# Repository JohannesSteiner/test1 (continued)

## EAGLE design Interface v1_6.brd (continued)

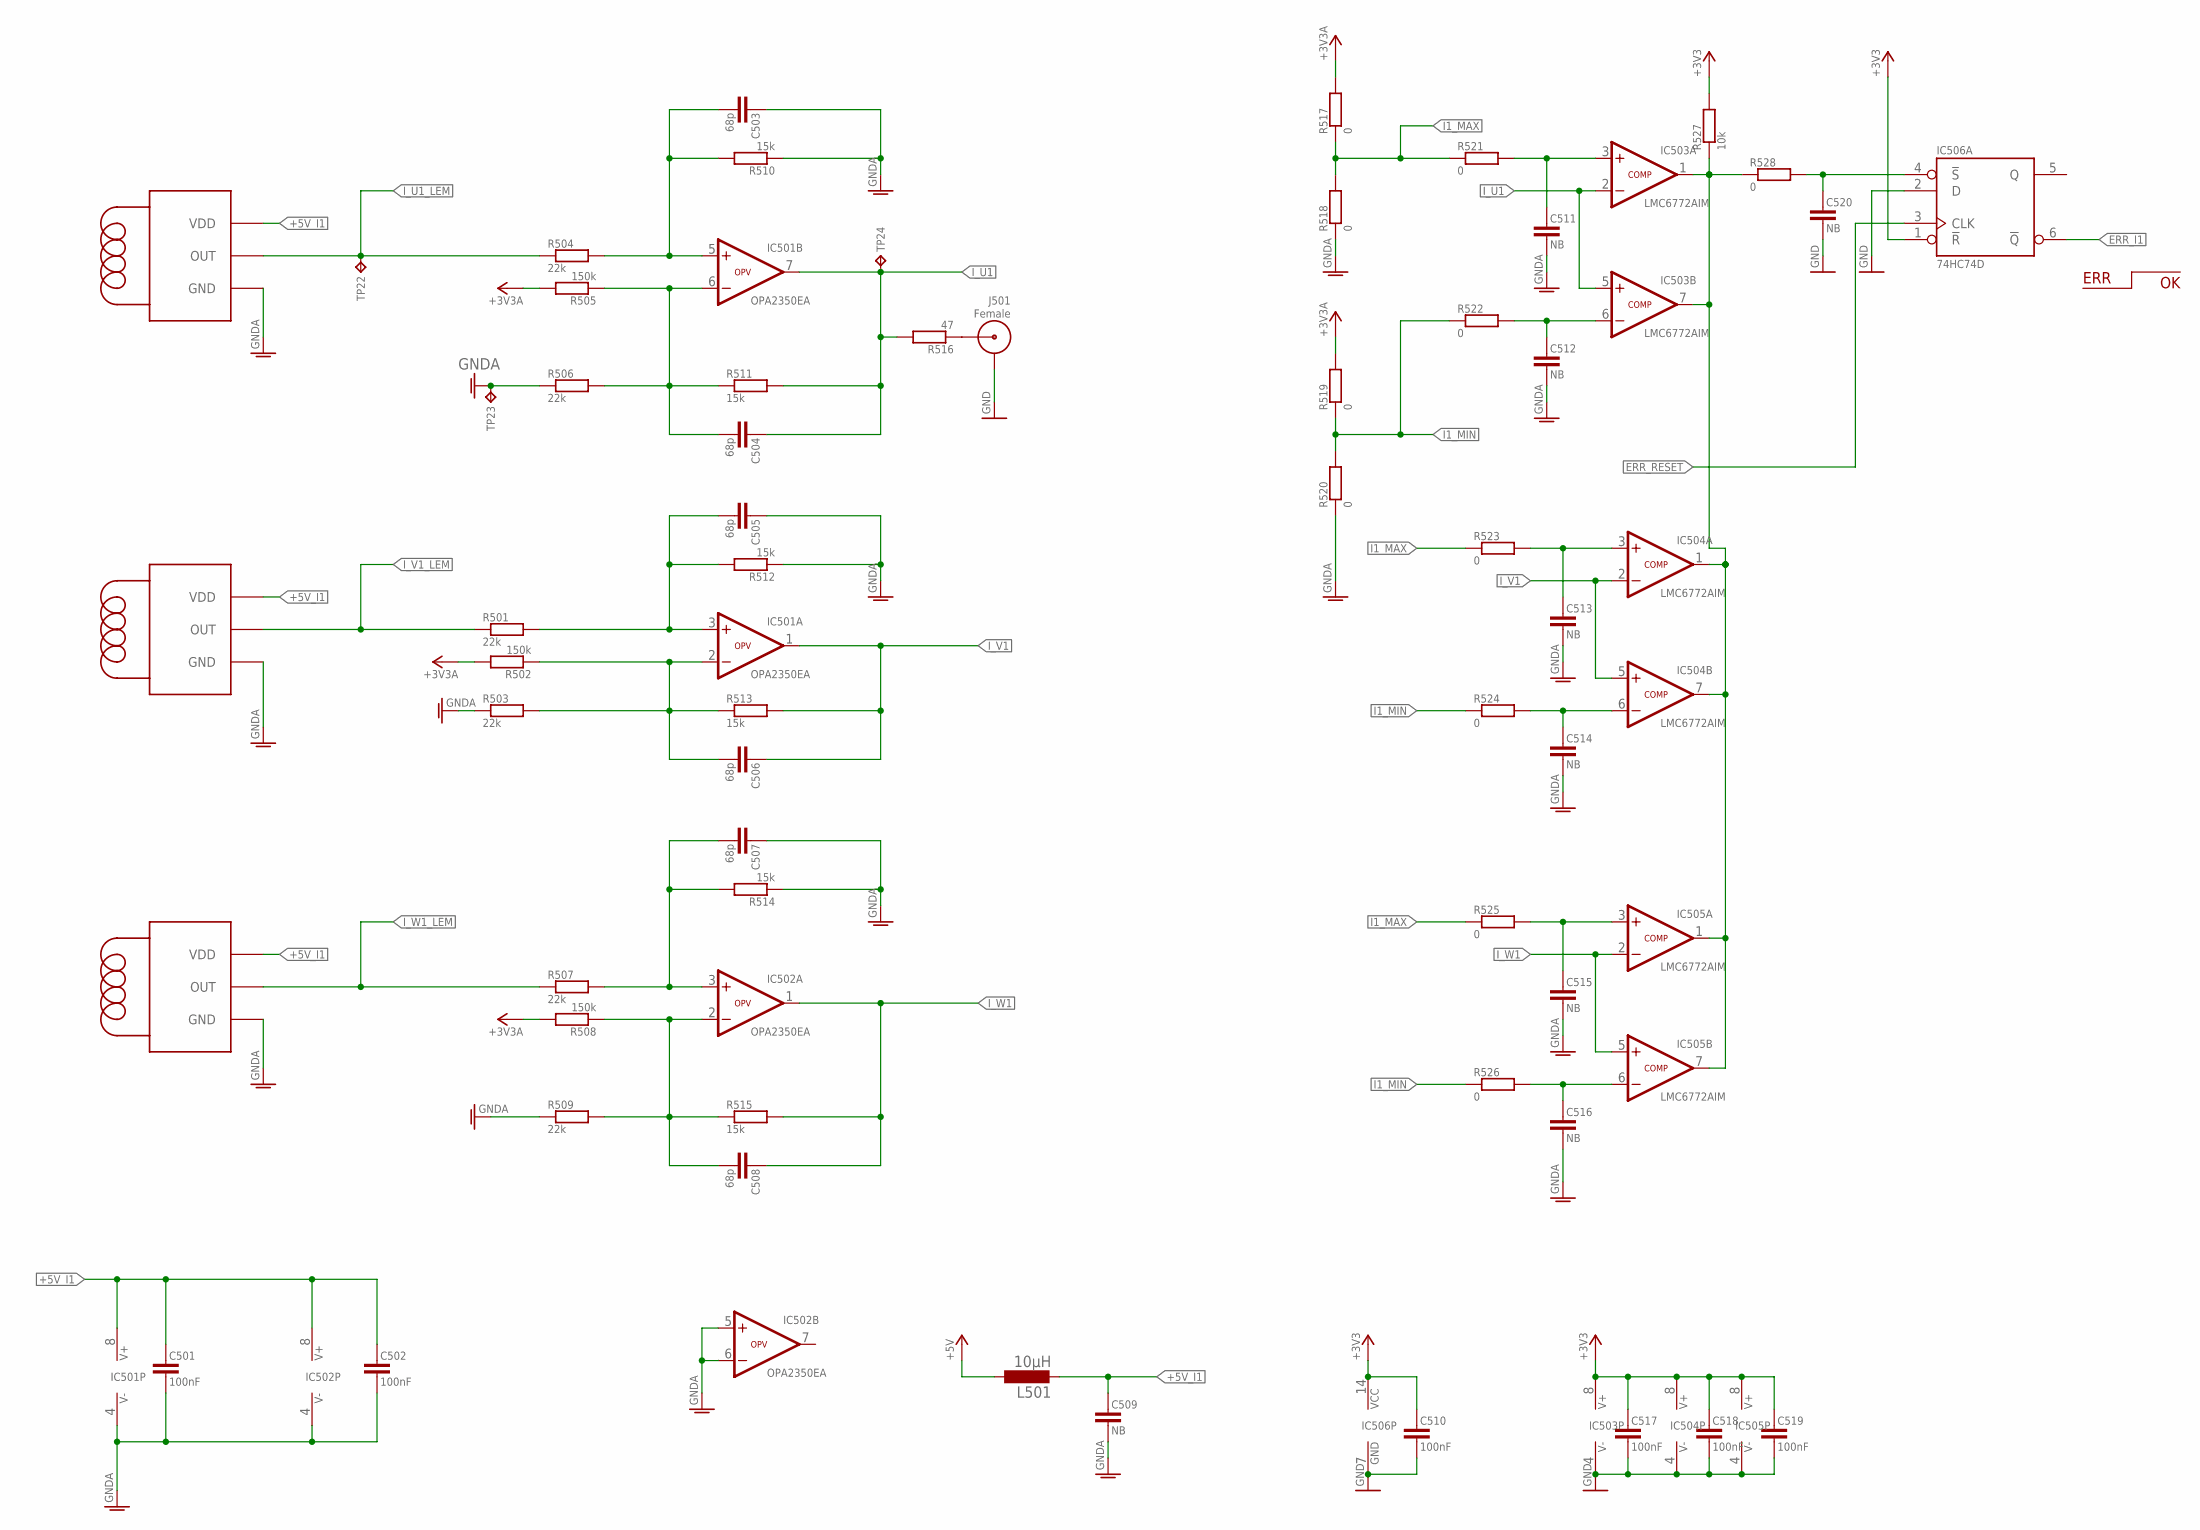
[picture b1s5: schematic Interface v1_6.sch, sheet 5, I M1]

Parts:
C501, C502, C510, C517, C518, C519: 100nF; C-0805"
C503, C504, C505, C506, C507, C508: 68p; C-0805"
C509, C511, C512, C513, C514, C515, C516, C520: NB; C-0805"
I501, I502, I503: HC2F
IC501, IC502: OPA2350EA; SOIC8
IC503, IC504, IC505: LMC6772AIM; SOIC8
IC506: 74HC74D; SOIC14
J501: Female; SMA_KLEIN
L501: 10µH; L3230M
R501, R503, R504, R506, R507, R509: 22k; R-0805"
R502, R505, R508: 150k; R-0805"
R510, R511, R512, R513, R514, R515: 15k; R-0805"
R516: 47; R-0805"
R517, R518, R519, R520, R521, R522, R523, R524, R525, R526, R528: 0; R-0805"
R527: 10k; R-0805"
TP22, TP24: TP-TH-08; TP-08
TP23: TP-TH-12; TP-12

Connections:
+3V3: C510.1, C517.1, C518.1, C519.1, IC503.8 (V+), IC504.8 (V+), IC505.8 (V+), IC506.1 (!R), IC506.14 (VCC), R527.2; also elsewhere on the board
+3V3A_I1: R502.2, R505.2, R508.2, R517.2, R519.2; also elsewhere on the board
+5V: L501.1; also elsewhere on the board
+5V_I1: C501.1, C502.1, C509.1, I501.3 (VDD), I502.3 (VDD), I503.3 (VDD), IC501.8 (V+), IC502.8 (V+), L501.2; also elsewhere on the board
ERR_I1: IC506.6 (!Q); also elsewhere on the board
ERR_RESET: IC506.3 (CLK); also elsewhere on the board
GND: C510.2, C517.2, C518.2, C519.2, C520.2, IC503.4 (V-), IC504.4 (V-), IC505.4 (V-), IC506.2 (D), IC506.7 (GND), J501.1 (GND), J501.3 (GND), J501.4 (GND), J501.5 (GND); also elsewhere on the board
GNDA: C501.2, C502.2, C503.1, C505.1, C507.1, C509.2, C511.2, C512.2, C513.2, C514.2, C515.2, C516.2, I501.2 (GND), I501.E1 (GND), I501.E2 (GND), I501.E3 (GND), I501.E4 (GND), I502.2 (GND), I502.E1 (GND), I502.E2 (GND), I502.E3 (GND), I502.E4 (GND), I503.2 (GND), I503.E1 (GND), I503.E2 (GND), I503.E3 (GND), I503.E4 (GND), IC501.4 (V-), IC502.4 (V-), IC502.5 (+IN), IC502.6 (-IN), R503.1, R506.1, R509.1, R510.1, R512.1, R514.1, R518.1, R520.1, TP23.TP; also elsewhere on the board
I1_MAX: R517.1, R518.2, R521.1, R523.1, R525.1
I1_MIN: R519.1, R520.2, R522.1, R524.1, R526.1
I_U1: C504.1, IC501.7 (OUT), IC503.2 (-IN), IC503.5 (+IN), R511.2, R516.2, TP24.TP; also elsewhere on the board
I_U1_LEM: I501.1 (OUT), R504.1, TP22.TP
I_V1: C506.1, IC501.1 (OUT), IC504.2 (-IN), IC504.5 (+IN), R513.2; also elsewhere on the board
I_V1_LEM: I502.1 (OUT), R501.1
I_W1: C508.1, IC502.1 (OUT), IC505.2 (-IN), IC505.5 (+IN), R515.2; also elsewhere on the board
I_W1_LEM: I503.1 (OUT), R507.1
MINUS: C508.2, IC502.2 (-IN), R508.1, R509.2, R515.1
unnamed: C503.2, IC501.5 (+IN), R504.2, R510.2
unnamed: C504.2, IC501.6 (-IN), R505.1, R506.2, R511.1
unnamed: C506.2, IC501.2 (-IN), R502.1, R503.2, R513.1
unnamed: J501.SIG, R516.1
unnamed: C505.2, IC501.3 (+IN), R501.2, R512.2
unnamed: C512.1, IC503.6 (-IN), R522.2
unnamed: C511.1, IC503.3 (+IN), R521.2
unnamed: C520.1, IC506.4 (!S), R528.2
unnamed: C514.1, IC504.6 (-IN), R524.2
unnamed: C513.1, IC504.3 (+IN), R523.2
unnamed: C515.1, IC505.3 (+IN), R525.2
unnamed: C516.1, IC505.6 (-IN), R526.2
OC_M1: IC503.1 (OUT), IC503.7 (OUT), IC504.1 (OUT), IC504.7 (OUT), IC505.1 (OUT), IC505.7 (OUT), R527.1, R528.1
PLUS: C507.2, IC502.3 (+IN), R507.2, R514.2

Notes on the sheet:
ERR

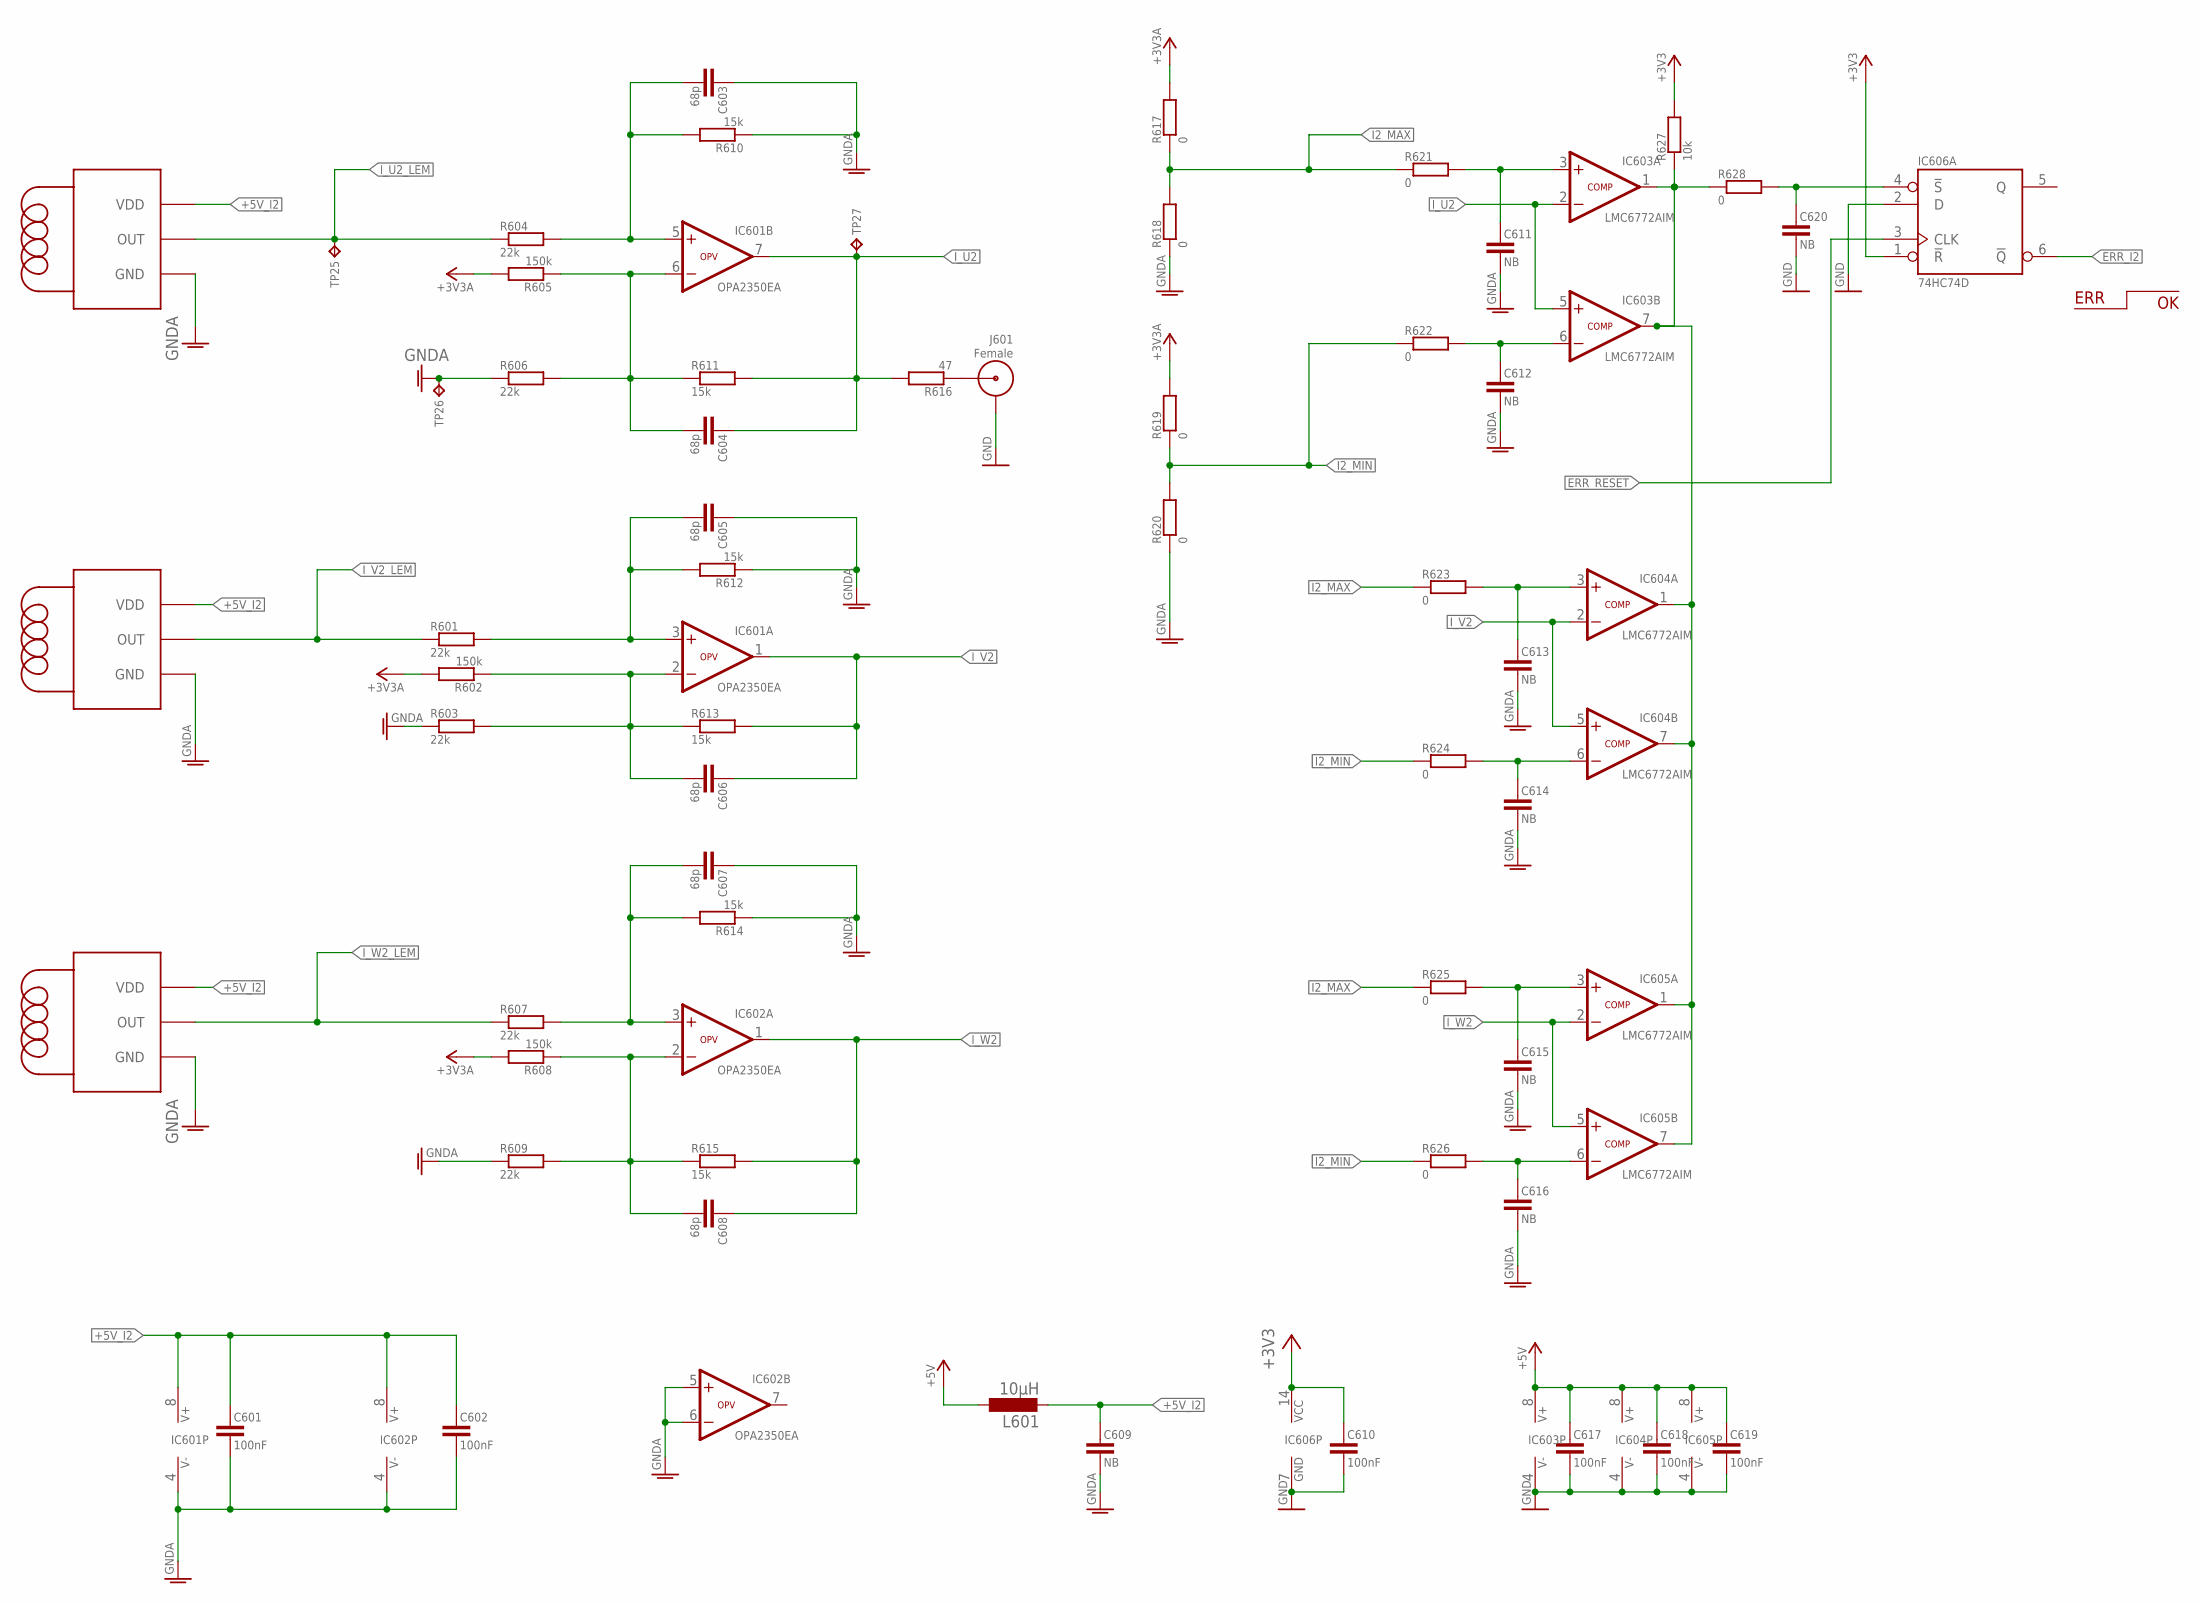
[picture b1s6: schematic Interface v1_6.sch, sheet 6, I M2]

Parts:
C601, C602, C610, C617, C618, C619: 100nF; C-0805"
C603, C604, C605, C606, C607, C608: 68p; C-0805"
C609, C611, C612, C613, C614, C615, C616, C620: NB; C-0805"
I601, I602, I603: HC2F
IC601, IC602: OPA2350EA; SOIC8
IC603, IC604, IC605: LMC6772AIM; SOIC8
IC606: 74HC74D; SOIC14
J601: Female; SMA_KLEIN
L601: 10µH; L3230M
R601, R603, R604, R606, R607, R609: 22k; R-0805"
R602, R605, R608: 150k; R-0805"
R610, R611, R612, R613, R614, R615: 15k; R-0805"
R616: 47; R-0805"
R617, R618, R619, R620, R621, R622, R623, R624, R625, R626, R628: 0; R-0805"
R627: 10k; R-0805"
TP25, TP27: TP-TH-08; TP-08
TP26: TP-TH-12; TP-12

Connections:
+3V3: C610.1, IC606.1 (!R), IC606.14 (VCC), R627.2; also elsewhere on the board
+3V3A_I2: R602.2, R605.2, R608.2, R617.2, R619.2; also elsewhere on the board
+5V: C617.1, C618.1, C619.1, IC603.8 (V+), IC604.8 (V+), IC605.8 (V+), L601.1; also elsewhere on the board
+5V_I2: C601.1, C602.1, C609.1, I601.3 (VDD), I602.3 (VDD), I603.3 (VDD), IC601.8 (V+), IC602.8 (V+), L601.2; also elsewhere on the board
ERR_I2: IC606.6 (!Q); also elsewhere on the board
ERR_RESET: IC606.3 (CLK); also elsewhere on the board
GND: C610.2, C617.2, C618.2, C619.2, C620.2, IC603.4 (V-), IC604.4 (V-), IC605.4 (V-), IC606.2 (D), IC606.7 (GND), J601.1 (GND), J601.3 (GND), J601.4 (GND), J601.5 (GND); also elsewhere on the board
GNDA: C601.2, C602.2, C603.1, C605.1, C607.1, C609.2, C611.2, C612.2, C613.2, C614.2, C615.2, C616.2, I601.2 (GND), I601.E1 (GND), I601.E2 (GND), I601.E3 (GND), I601.E4 (GND), I602.2 (GND), I602.E1 (GND), I602.E2 (GND), I602.E3 (GND), I602.E4 (GND), I603.2 (GND), I603.E1 (GND), I603.E2 (GND), I603.E3 (GND), I603.E4 (GND), IC601.4 (V-), IC602.4 (V-), IC602.5 (+IN), IC602.6 (-IN), R603.1, R606.1, R609.1, R610.1, R612.1, R614.1, R618.1, R620.1, TP26.TP; also elsewhere on the board
I2_MAX: R617.1, R618.2, R621.1, R623.1, R625.1
I2_MIN: R619.1, R620.2, R622.1, R624.1, R626.1
I_U2: C604.1, IC601.7 (OUT), IC603.2 (-IN), IC603.5 (+IN), R611.2, R616.2, TP27.TP; also elsewhere on the board
I_U2_LEM: I601.1 (OUT), R604.1, TP25.TP
I_V2: C606.1, IC601.1 (OUT), IC604.2 (-IN), IC604.5 (+IN), R613.2; also elsewhere on the board
I_V2_LEM: I602.1 (OUT), R601.1
I_W2: C608.1, IC602.1 (OUT), IC605.2 (-IN), IC605.5 (+IN), R615.2; also elsewhere on the board
I_W2_LEM: I603.1 (OUT), R607.1
MINUS2: C608.2, IC602.2 (-IN), R608.1, R609.2, R615.1
unnamed: C612.1, IC603.6 (-IN), R622.2
unnamed: C611.1, IC603.3 (+IN), R621.2
unnamed: C620.1, IC606.4 (!S), R628.2
unnamed: C614.1, IC604.6 (-IN), R624.2
unnamed: C613.1, IC604.3 (+IN), R623.2
unnamed: C615.1, IC605.3 (+IN), R625.2
unnamed: C616.1, IC605.6 (-IN), R626.2
unnamed: C604.2, IC601.6 (-IN), R605.1, R606.2, R611.1
unnamed: C603.2, IC601.5 (+IN), R604.2, R610.2
unnamed: C606.2, IC601.2 (-IN), R602.1, R603.2, R613.1
unnamed: C605.2, IC601.3 (+IN), R601.2, R612.2
unnamed: J601.SIG, R616.1
OC_M2: IC603.1 (OUT), IC603.7 (OUT), IC604.1 (OUT), IC604.7 (OUT), IC605.1 (OUT), IC605.7 (OUT), R627.1, R628.1
PLUS2: C607.2, IC602.3 (+IN), R607.2, R614.2

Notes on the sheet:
ERR

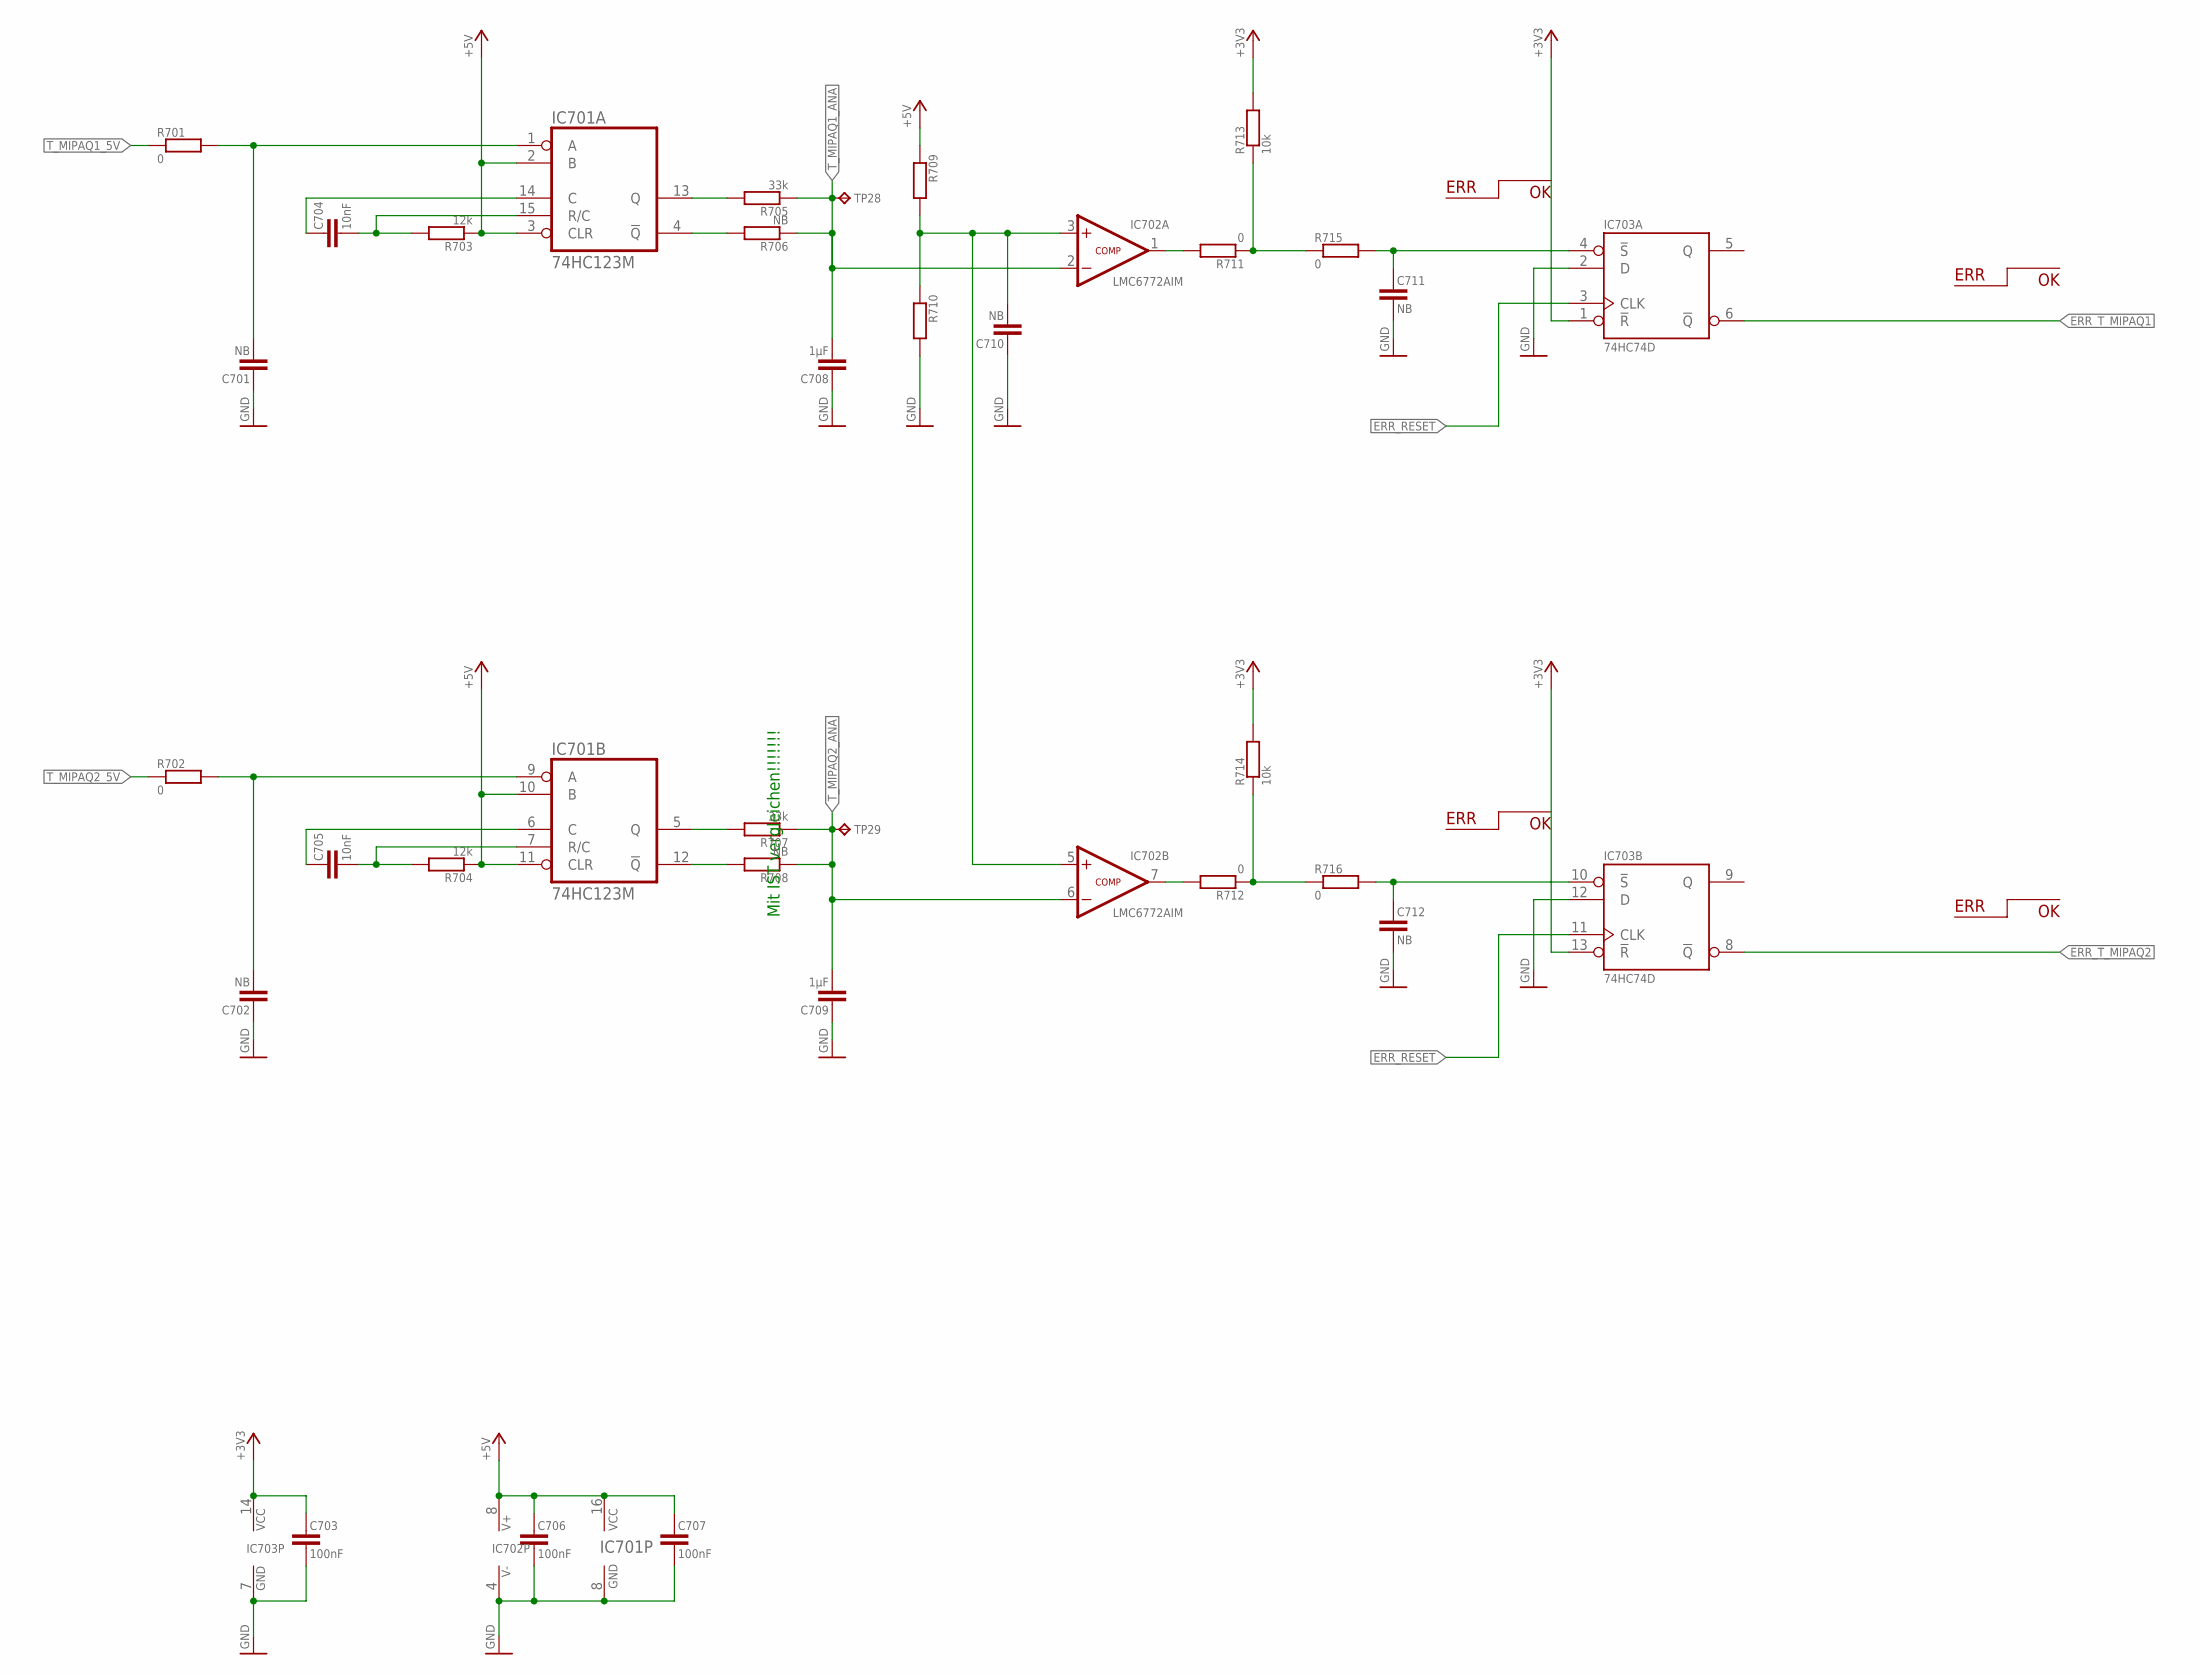
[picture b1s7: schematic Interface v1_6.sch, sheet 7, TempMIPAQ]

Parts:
C701, C702, C710, C711, C712: NB; C-0805"
C703, C706, C707: 100nF; C-0805"
C704, C705: 10nF; C-0805"
C708, C709: 1µF; C-0805"
IC701: 74HC123M; SO16
IC702: LMC6772AIM; SOIC8
IC703: 74HC74D; SOIC14
R701, R702, R711, R712, R715, R716: 0; R-0805"
R703, R704: 12k; R-0805"
R705, R707: 33k; R-0805"
R706, R708: NB; R-0805"
R709, R710: R-0805"
R713, R714: 10k; R-0805"
TP28, TP29: TP-TH-08; TP-08

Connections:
+3V3: C703.1, IC703.1 (!R), IC703.13 (!R), IC703.14 (VCC), R713.2, R714.2; also elsewhere on the board
+5V: C706.1, C707.1, IC701.2 (B), IC701.3 (CLR), IC701.10 (B), IC701.11 (CLR), IC701.16 (VCC), IC702.8 (V+), R703.1, R704.1, R709.1; also elsewhere on the board
ERR_RESET: IC703.3 (CLK), IC703.11 (CLK); also elsewhere on the board
ERR_T_MIPAQ1: IC703.6 (!Q); also elsewhere on the board
ERR_T_MIPAQ2: IC703.8 (!Q); also elsewhere on the board
GND: C701.1, C702.1, C703.2, C706.2, C707.2, C708.1, C709.1, C710.1, C711.2, C712.2, IC701.8 (GND), IC702.4 (V-), IC703.2 (D), IC703.7 (GND), IC703.12 (D), R710.2; also elsewhere on the board
unnamed: IC702.7 (OUT), R712.2
unnamed: IC702.1 (OUT), R711.2
unnamed: C702.2, IC701.9 (A), R702.2
unnamed: IC701.13 (Q), R705.2
unnamed: C701.2, IC701.1 (A), R701.2
unnamed: C704.2, IC701.15 (R/C), R703.2
unnamed: IC701.4 (!Q), R706.2
unnamed: C710.2, IC702.3 (+IN), IC702.5 (+IN), R709.2, R710.1
unnamed: R711.1, R713.1, R715.1
unnamed: C704.1, IC701.14 (C)
unnamed: C705.2, IC701.7 (R/C), R704.2
unnamed: IC701.5 (Q), R707.2
unnamed: IC701.12 (!Q), R708.2
unnamed: C712.1, IC703.10 (!S), R716.2
unnamed: C705.1, IC701.6 (C)
unnamed: R712.1, R714.1, R716.1
unnamed: C711.1, IC703.4 (!S), R715.2
T_MIPAQ1_5V: R701.1; also elsewhere on the board
T_MIPAQ1_ANA: C708.2, IC702.2 (-IN), R705.1, R706.1, TP28.TP; also elsewhere on the board
T_MIPAQ2_5V: R702.1; also elsewhere on the board
T_MIPAQ2_ANA: C709.2, IC702.6 (-IN), R707.1, R708.1, TP29.TP; also elsewhere on the board

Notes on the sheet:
ERR
Mit IST vergleichen!!!!!!!

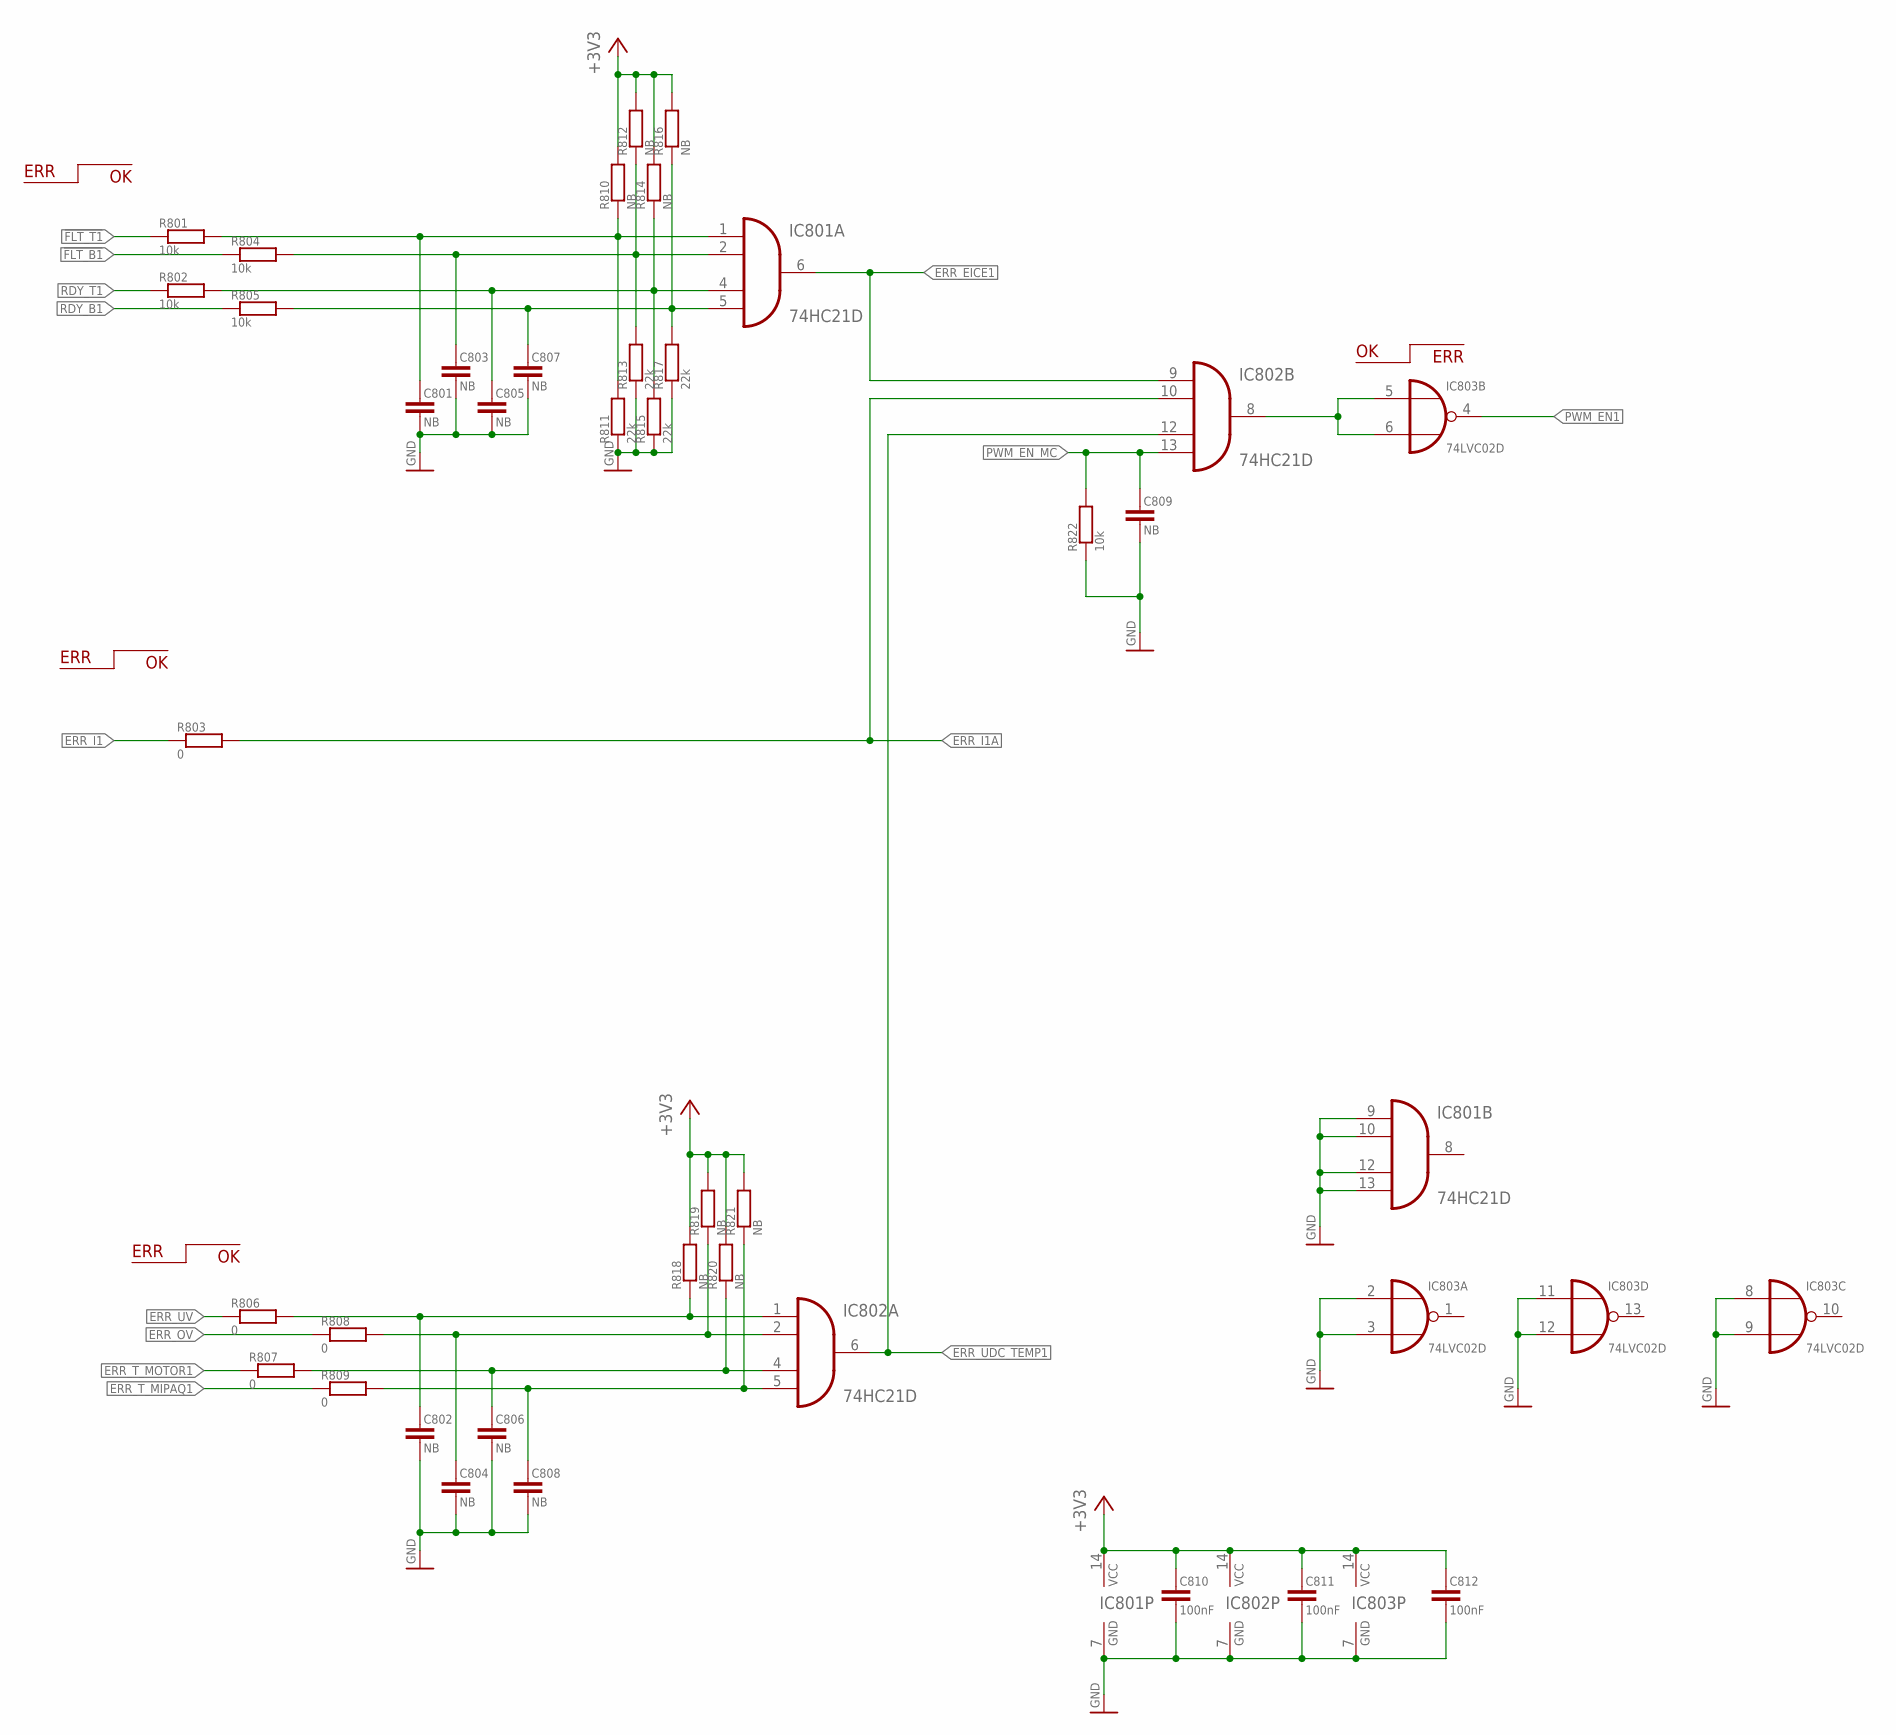
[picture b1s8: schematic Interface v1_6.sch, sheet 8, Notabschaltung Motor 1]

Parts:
C801, C802, C803, C804, C805, C806, C807, C808, C809: NB; C-0805"
C810, C811, C812: 100nF; C-0805"
IC801, IC802: 74HC21D; SOIC14
IC803: 74LVC02D; SOIC14
R801, R802, R804, R805, R822: 10k; R-0805"
R803, R806, R807, R808, R809: 0; R-0805"
R810, R812, R814, R816, R818, R819, R820, R821: NB; R-0805"
R811, R813, R815, R817: 22k; R-0805"

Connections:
!FLT_B1: R804.1; also elsewhere on the board
!FLT_T1: R801.1; also elsewhere on the board
+3V3: C810.1, C811.1, C812.1, IC801.14 (VCC), IC802.14 (VCC), IC803.14 (VCC), R810.2, R812.2, R814.2, R816.2, R818.2, R819.2, R820.2, R821.2; also elsewhere on the board
ERR_EICE1: IC801.6 (O), IC802.9 (I0)
ERR_I1: R803.1; also elsewhere on the board
ERR_I1A: IC802.10 (I1), R803.2
ERR_OV: R808.1; also elsewhere on the board
ERR_T_MIPAQ1: R809.1; also elsewhere on the board
ERR_T_MOTOR1: R807.1; also elsewhere on the board
ERR_UDC_TEMP1: IC802.6 (O), IC802.12 (I2); also elsewhere on the board
ERR_UV: R806.1; also elsewhere on the board
GND: C801.2, C802.2, C803.2, C804.2, C805.2, C806.2, C807.2, C808.2, C809.2, C810.2, C811.2, C812.2, IC801.7 (GND), IC801.9 (I0), IC801.10 (I1), IC801.12 (I2), IC801.13 (I3), IC802.7 (GND), IC803.2 (I0), IC803.3 (I1), IC803.7 (GND), IC803.8 (I0), IC803.9 (I1), IC803.11 (I0), IC803.12 (I1), R811.1, R813.1, R815.1, R817.1, R822.1; also elsewhere on the board
unnamed: C801.1, IC801.1 (I0), R801.2, R810.1, R811.2
unnamed: C805.1, IC801.4 (I2), R802.2, R814.1, R815.2
unnamed: C807.1, IC801.5 (I3), R805.2, R816.1, R817.2
unnamed: C802.1, IC802.1 (I0), R806.2, R818.1
unnamed: C804.1, IC802.2 (I1), R808.2, R819.1
unnamed: C806.1, IC802.4 (I2), R807.2, R820.1
unnamed: C808.1, IC802.5 (I3), R809.2, R821.1
unnamed: IC802.8 (O), IC803.5 (I0), IC803.6 (I1)
unnamed: C803.1, IC801.2 (I1), R804.2, R812.1, R813.2
PWM_EN1: IC803.4 (O); also elsewhere on the board
PWM_EN_MC: C809.1, IC802.13 (I3), R822.2; also elsewhere on the board
RDY_B1: R805.1; also elsewhere on the board
RDY_T1: R802.1; also elsewhere on the board

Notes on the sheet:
ERR

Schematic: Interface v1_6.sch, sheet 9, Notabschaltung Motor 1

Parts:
C901, C902, C903, C904, C905, C906, C907, C908: NB; C-0805"
C909, C910, C911: 100nF; C-0805"
IC901, IC902: 74HC21D; SOIC14
IC903: 74LVC02D; SOIC14
R901, R902, R904, R905: 10k; R-0805"
R903, R906, R907, R908, R909: 0; R-0805"
R910, R912, R914, R916, R918, R919, R920, R921: NB; R-0805"
R911, R913, R915, R917: 22k; R-0805"

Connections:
!FLT_B2: R905.1; also elsewhere on the board
!FLT_T2: R901.1; also elsewhere on the board
+3V3: C909.1, C910.1, C911.1, IC901.14 (VCC), IC902.14 (VCC), IC903.14 (VCC), R910.2, R912.2, R914.2, R916.2, R918.2, R919.2, R920.2, R921.2; also elsewhere on the board
ERR_EICE2: IC901.6 (O), IC902.9 (I0)
ERR_I2: R903.1; also elsewhere on the board
ERR_I2A: IC902.12 (I2), R903.2; also elsewhere on the board
ERR_OV: R908.1; also elsewhere on the board
ERR_T_MIPAQ2: R909.1; also elsewhere on the board
ERR_T_MOTOR2: R906.1; also elsewhere on the board
ERR_UDC_TEMP2: IC902.6 (O), IC902.10 (I1); also elsewhere on the board
ERR_UV: R907.1; also elsewhere on the board
GND: C901.2, C902.2, C903.2, C904.2, C905.2, C906.2, C907.2, C908.2, C909.2, C910.2, C911.2, IC901.7 (GND), IC901.9 (I0), IC901.10 (I1), IC901.12 (I2), IC901.13 (I3), IC902.7 (GND), IC903.2 (I0), IC903.3 (I1), IC903.5 (I0), IC903.6 (I1), IC903.7 (GND), IC903.11 (I0), IC903.12 (I1), R911.1, R913.1, R915.1, R917.1; also elsewhere on the board
unnamed: C901.1, IC901.1 (I0), R901.2, R910.1, R911.2
unnamed: C905.1, IC901.4 (I2), R902.2, R914.1, R915.2
unnamed: C907.1, IC901.5 (I3), R905.2, R916.1, R917.2
unnamed: C902.1, IC902.1 (I0), R906.2, R918.1
unnamed: C904.1, IC902.2 (I1), R908.2, R919.1
unnamed: C906.1, IC902.4 (I2), R907.2, R920.1
unnamed: C908.1, IC902.5 (I3), R909.2, R921.1
unnamed: C903.1, IC901.2 (I1), R904.2, R912.1, R913.2
unnamed: IC902.8 (O), IC903.8 (I0), IC903.9 (I1)
PWM_EN2: IC903.10 (O); also elsewhere on the board
PWM_EN_MC: IC902.13 (I3); also elsewhere on the board
RDY_B2: R902.1; also elsewhere on the board
RDY_T2: R904.1; also elsewhere on the board

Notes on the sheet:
ERR
